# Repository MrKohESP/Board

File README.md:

# Mr. Koh Board
Mr. Koh ESP32-C3 RISC-V Development Board

## The Mr. Koh is a birthday project for Mr. Koh.
# Happy Birthday Mr. Koh! 🥳
Mr. Koh is an Open Hardware, Open Source (GPL3.0), ESP32-C3 RISC-V Developement Board.

## Features
* [RISC-V](https://github.com/jameslzhu/riscv-card/blob/586b60b5c351b3e6e6ebbf7130b9f93013b2e511/riscv-card.pdf) instruction set
* [Espressif Systems ESP32-C3FH4 MCU](https://www.espressif.com/en/products/socs/esp32-c3)
* 400K SDRAM and 4MB Flash memory
* Real-Time Clock support
* 10 GPIOs with RESET, BOOT, and RGB OUT
* [RGB](http://www.world-semi.com/Certifications/details-111-4.html), power and data leds
* Built-in USB Type C flashing and [JTAG debugging](https://docs.espressif.com/projects/esp-idf/en/latest/esp32c3/api-guides/usb-serial-jtag-console.html)
* ESD protected
* [FreeRTOS](https://www.freertos.org/Using-FreeRTOS-on-RISC-V.html) Supported when using [ESP-IDF](https://docs.espressif.com/projects/esp-idf/en/v5.0/esp32/)

## Pinout

## Files
* [Datasheet](https://www.espressif.com/sites/default/files/documentation/esp32-c3_datasheet_en.pdf)
* [Schematic](Schematic.pdf) 
* [BOM](Hardware/Fab/MrKohBOM.csv)
* [CPL (Position)](Hardware/Fab/MrKoh-top-pos.csv)
* [PCB Front](MrKoh.png)
* [PCB Back](MrKohBack.png)

## History
1. v1 Designed 01/23/2023.
2. v1 Sent to production 01/26/2023.
3. v1 Shipped 01/30/2023.
4. v1 Arrival 02/03/2023.
5. v1 Issues with USB Type C connector clearance and USB Type C pinout resulting in connectivity problems.
6. v1 LED was on all the time.
7. Rev 2 Carved out a space for the Type C connector and redid the PCB for correct pinout.
8. Rev 2 Removed Q1 and pull up, Pin GPIO2 is now just an LED.  Reworked PCB to remove Q1 and R7. 
9. Rev 2 Reworked the Pin Header pins to allow 5V from USB and to use that pin in place of USB.
10. Rev 2 Sent to production 02/06/2023, Shenzhen, Guangdong, China Time (UTC+8).
11. Rev 2 pcb finished 02/07/2023
12. Rev 2 assembly finished 2023-02-08 06:37:05 (local time).
13. Rev 2 waiting for Carrier to pick up completed boards.
14. Rev 2 delivered on Mon Feb 13 at 16:43
15. Rev 2 Tests indicate board is fully functional.

## Photo

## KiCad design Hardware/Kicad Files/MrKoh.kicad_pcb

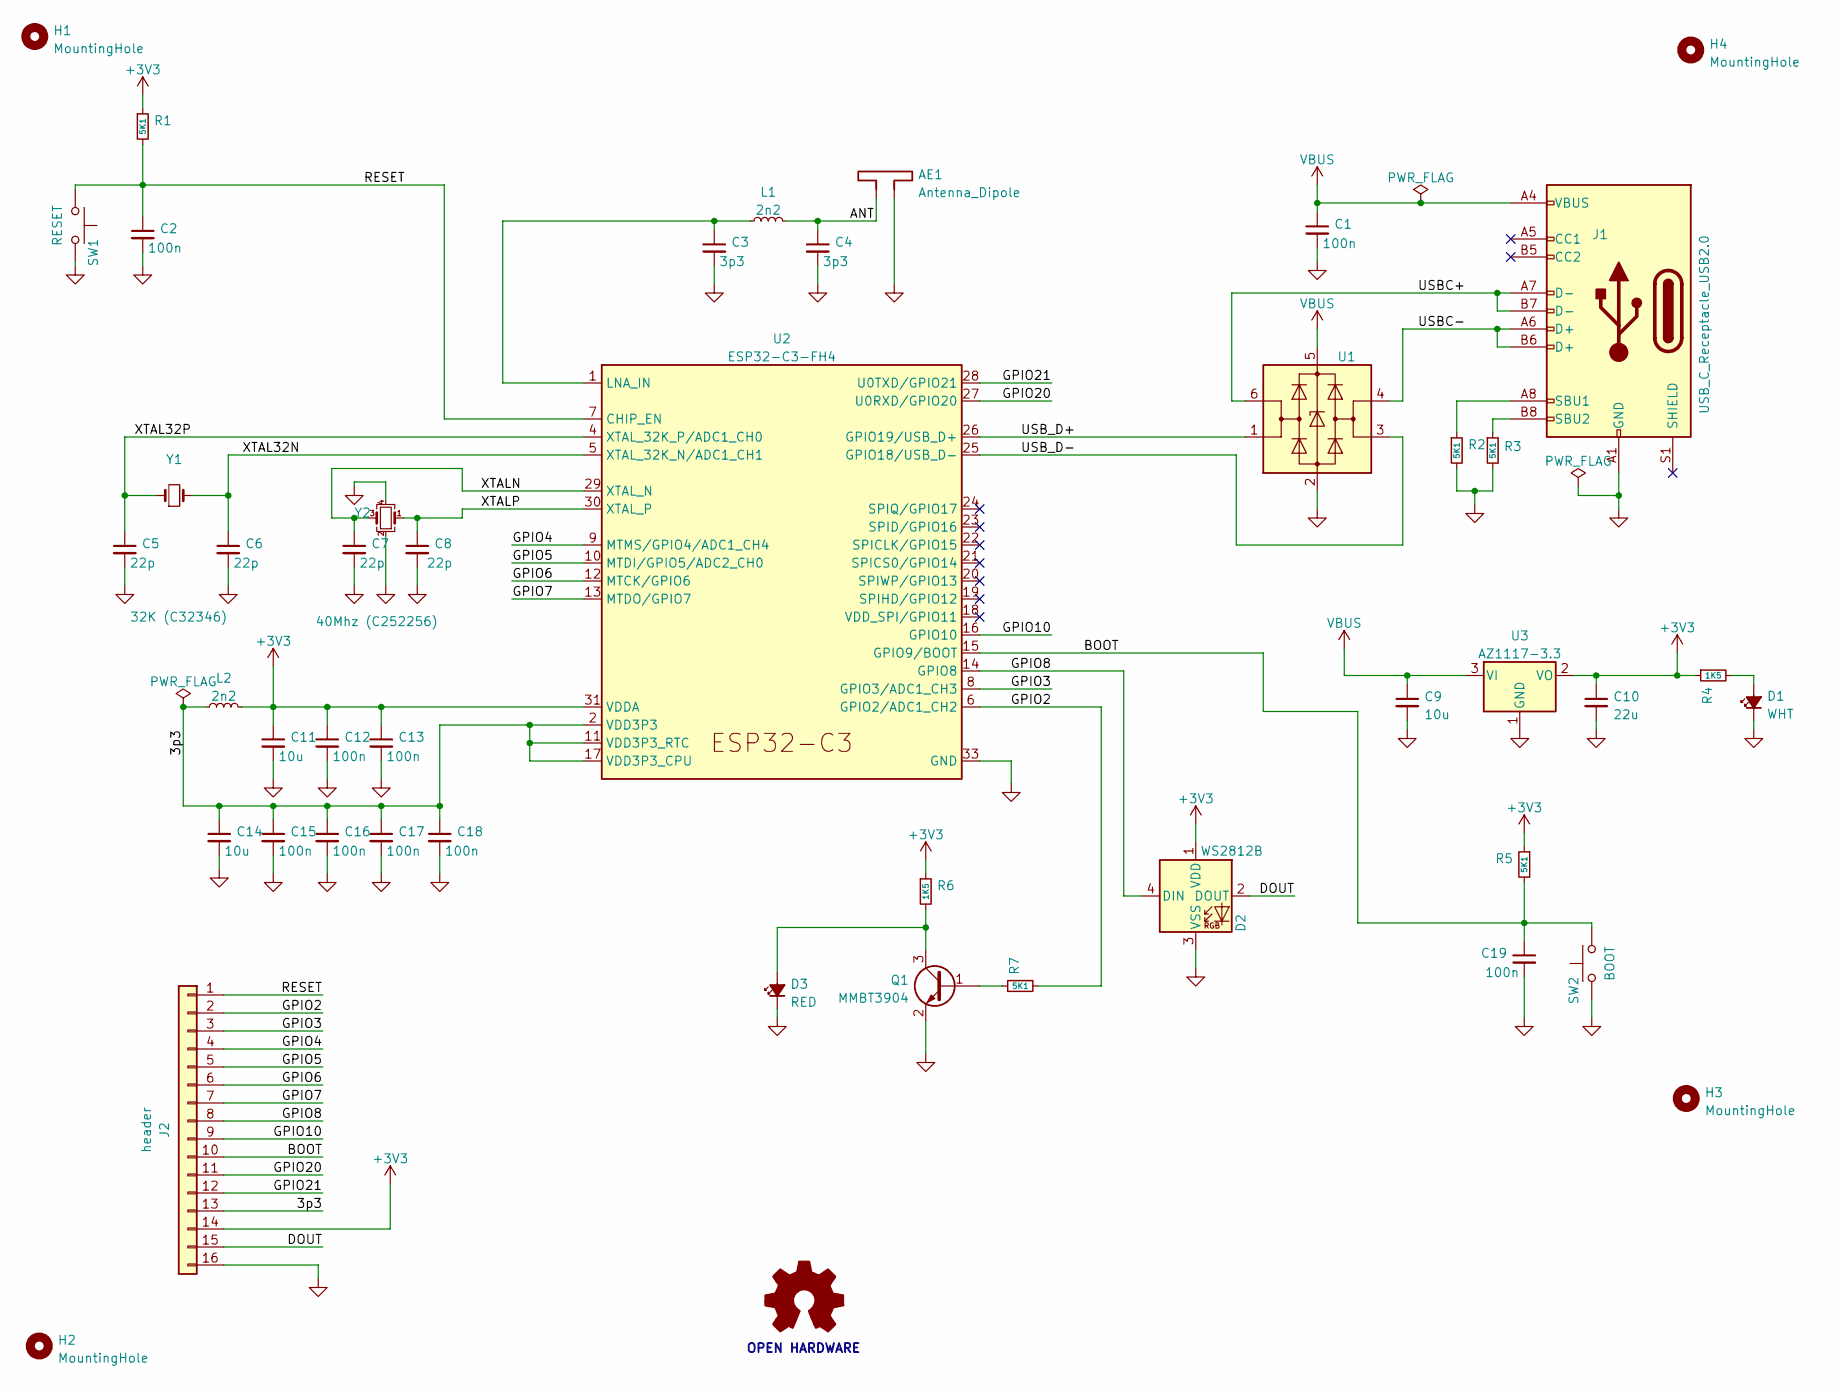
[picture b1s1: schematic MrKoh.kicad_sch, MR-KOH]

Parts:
AE1: Antenna_Dipole; Texas_SWRA117D_2.4GHz_Left
C1, C2, C12, C13, C15, C16, C17, C18, C19: 100n; C_0402_1005Metric; LCSC C60474
C3, C4: 3p3; C_0402_1005Metric; LCSC C1565
C5, C6, C7, C8: 22p; C_0402_1005Metric; LCSC C1555
C9, C11, C14: 10u; C_0603_1608Metric; LCSC C96446
C10: 22u; C_0805_2012Metric; LCSC C45783
D1: WHT; LED_0603_1608Metric; LCSC C2286
D2: WS2812B; LED_WS2812B_PLCC4_5.0x5.0mm_P3.2mm
D3: RED; LED_0603_1608Metric; LCSC C2290
H1, H2, H3, H4: MountingHole; MountingHole_1152_JLCPCB
J1: USB_C_Receptacle_USB2.0; USB_C_Receptacle_HRO_TYPE-C-31-M-12; LCSC C165948
J2: header; PinHeader_1x16_P2.54mm_Vertical
L1, L2: 2n2; L_0402_1005Metric; LCSC C76790
LOGO1: Logo_Open_Hardware_Small; Symbol_GNU-Logo_SilkscreenTop
Q1: MMBT3904; SOT-23; LCSC C20526
R1, R2, R3, R5, R7: 5K1; R_0402_1005Metric; LCSC C25905
R4, R6: 1K5; R_0402_1005Metric; LCSC C25867
SW1: RESET; SW_Push_SPST_NO_Alps_SKRK; LCSC C202388
SW2: BOOT; SW_Push_SPST_NO_Alps_SKRK; LCSC C202388
U1: USBLC6-2SC6; SOT-23-6; LCSC C7519
U2: ESP32-C3-FH4; QFN-32-1EP_5x5mm_P0.5mm_EP3.45x3.45mm; LCSC C2858491
U3: AZ1117-3.3; SOT-223-3_TabPin2; LCSC C92517
Y1: 32K (C32346); Crystal_SMD_3215-2Pin_3.2x1.5mm; LCSC C32346
Y2: 40Mhz (C252256); Crystal_SMD_3225-4Pin_3.2x2.5mm; LCSC C252256

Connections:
+3V3: C10.1, C11.1, C12.1, C13.1, D2.1 (VDD), J2.14, L2.2, R1.1, R4.1, R5.1, R6.1, U2.31 (VDDA), U2.32 (VDDA), U3.2 (VO)
/3p3: C14.1, C15.1, C16.1, C17.1, C18.1, J2.13, L2.1, U2.2 (VDD3P3), U2.3 (VDD3P3), U2.11 (VDD3P3_RTC), U2.17 (VDD3P3_CPU)
/ANT: AE1.1, C4.1, L1.2
/BOOT: C19.1, J2.10, R5.2, SW2.1, U2.15 (GPIO9/BOOT)
/DOUT: D2.2 (DOUT), J2.15
/GPIO2: J2.2, R7.2, U2.6 (GPIO2/ADC1_CH2)
/GPIO3: J2.3, U2.8 (GPIO3/ADC1_CH3)
/GPIO4: J2.4, U2.9 (MTMS/GPIO4/ADC1_CH4)
/GPIO5: J2.5, U2.10 (MTDI/GPIO5/ADC2_CH0)
/GPIO6: J2.6, U2.12 (MTCK/GPIO6)
/GPIO7: J2.7, U2.13 (MTDO/GPIO7)
/GPIO8: D2.4 (DIN), J2.8, U2.14 (GPIO8)
/GPIO10: J2.9, U2.16 (GPIO10)
/GPIO20: J2.11, U2.27 (U0RXD/GPIO20)
/GPIO21: J2.12, U2.28 (U0TXD/GPIO21)
/RESET: C2.1, J2.1, R1.2, SW1.1, U2.7 (CHIP_EN)
/USBC+: J1.A7 (D-), J1.B7 (D-), U1.6 (I/O1)
/USBC-: J1.A6 (D+), J1.B6 (D+), U1.4 (I/O2)
/USB_D+: U1.1 (I/O1), U2.26 (GPIO19/USB_D+)
/USB_D-: U1.3 (I/O2), U2.25 (GPIO18/USB_D-)
/XTAL32N: C6.1, U2.5 (XTAL_32K_N/ADC1_CH1), Y1.2
/XTAL32P: C5.1, U2.4 (XTAL_32K_P/ADC1_CH0), Y1.1
/XTALN: C7.1, U2.29 (XTAL_N), Y2.3
/XTALP: C8.1, U2.30 (XTAL_P), Y2.1
GND: AE1.2, C1.2, C2.2, C3.2, C4.2, C5.2, C6.2, C7.2, C8.2, C9.2, C10.2, C11.2, C12.2, C13.2, C14.2, C15.2, C16.2, C17.2, C18.2, C19.2, D1.1 (K), D2.3 (VSS), D3.1 (K), J1.A1 (GND), J1.A12 (GND), J1.B1 (GND), J1.B12 (GND), J2.16, Q1.2 (E), R2.2, R3.2, SW1.2, SW2.2, U1.2 (GND), U2.33 (GND), U3.1 (GND), Y2.2, Y2.4
unnamed: C3.1, L1.1, U2.1 (LNA_IN)
unnamed: D1.2 (A), R4.2
unnamed: D3.2 (A), Q1.3 (C), R6.2
unnamed: J1.A8 (SBU1), R2.1
unnamed: J1.B8 (SBU2), R3.1
unnamed: Q1.1 (B), R7.1
VBUS: C1.1, C9.1, J1.A4 (VBUS), J1.A9 (VBUS), J1.B4 (VBUS), J1.B9 (VBUS), U1.5 (VBUS), U3.3 (VI)

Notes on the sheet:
OPEN HARDWARE

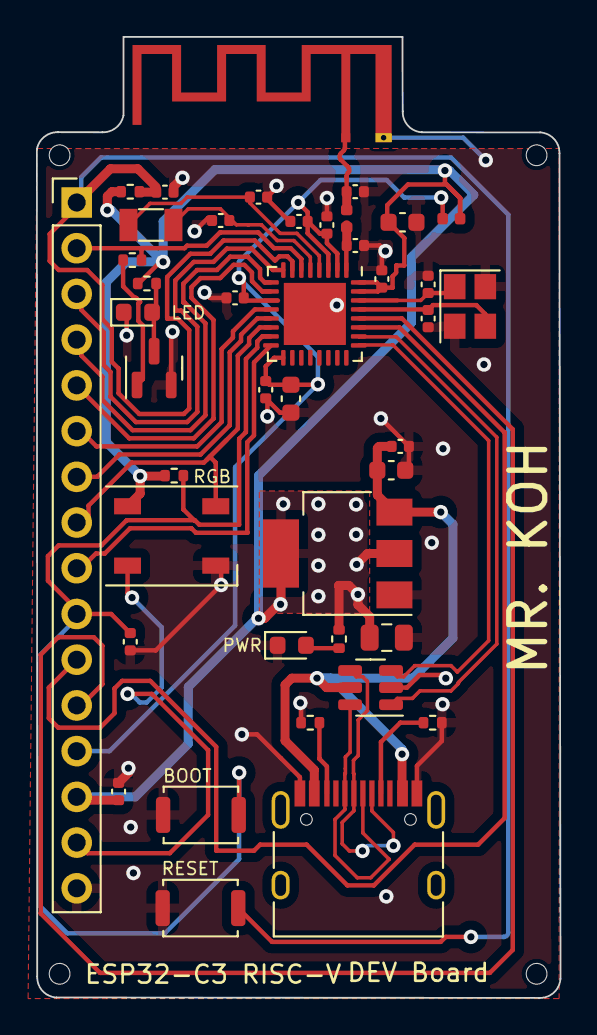
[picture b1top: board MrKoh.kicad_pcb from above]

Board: 2 copper layers, 29.1 x 53.4 mm, 47 parts (1 on the bottom side), 32 nets.

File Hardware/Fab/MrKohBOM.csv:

Comment,Designator,Footprint,LCSC
100n,"C1,C2,C12,C13,C15,C16,C17,C18,C19",Capacitor_SMD:C_0402_1005Metric,C60474
22u,C10,Capacitor_SMD:C_0805_2012Metric,C45783
3p3,"C3,C4",Capacitor_SMD:C_0402_1005Metric,C1565
22p,"C5,C6,C7,C8",Capacitor_SMD:C_0402_1005Metric,C1555
10u,"C9,C11,C14",Capacitor_SMD:C_0603_1608Metric,C96446
USB_C_Receptacle_USB2.0,J1,Connector_USB:USB_C_Receptacle_HRO_TYPE-C-31-M-12,C165948
2n2,"L1,L2",Inductor_SMD:L_0402_1005Metric,C76790
MMBT3904,Q1,Package_TO_SOT_SMD:SOT-23,C20526
5K1,"R1,R2,R3,R5",Resistor_SMD:R_0402_1005Metric,C25905
1K5,"R4,R6",Resistor_SMD:R_0402_1005Metric,C25867
RESET,SW1,Button_Switch_SMD:SW_Push_SPST_NO_Alps_SKRK,C202388
BOOT,SW2,Button_Switch_SMD:SW_Push_SPST_NO_Alps_SKRK,C202388
USBLC6-2SC6,U1,Package_TO_SOT_SMD:SOT-23-6,C7519
ESP32-C3-FH4,U2,Package_DFN_QFN:QFN-32-1EP_5x5mm_P0.5mm_EP3.45x3.45mm,C2858491
AZ1117-3.3,U3,Package_TO_SOT_SMD:SOT-223-3_TabPin2,C92517
32K (C32346),Y1,Crystal:Crystal_SMD_3215-2Pin_3.2x1.5mm,C32346
40Mhz (C252256),Y2,Crystal:Crystal_SMD_3225-4Pin_3.2x2.5mm,C252256
WHT,D1,LED_SMD:LED_0603_1608Metric,C2286
RED,D3,LED_SMD:LED_0603_1608Metric,C2290
WS2812B,D2,LED_SMD:LED_WS2812B_PLCC4_5.0x5.0mm_P3.2mm,C2843785

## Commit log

2023-01-26 Add Board 3D Images
2023-01-26 Added Image
2023-01-26 Schematic
2023-01-26 Fabrication Files
    Fab Files from original order
2023-01-26 Fabrication Files added
    Fab Files From Original Order
2023-01-26 Part issue
    There was a problem with sourcing the original RGB part and changes to schematic, pcb, and fabrication files. Production proofs were added.
2023-01-26 Production time 3d images
2023-01-26 New Part
2023-01-26 Rotate
2023-01-26 Production Zip
    Note changes to the csv files are not updated in the zip file but were uploaded after the fact in the bom and pos order proccess.
2023-01-27 Rename Hardware/Fabrication Files/espc4synth-B_Cu.gbl to Hardware/Fab/MrKoh.gbl
2023-01-27 Rename Hardware/Fabrication Files/espc4synth-B_Mask.gbs to Hardware/Fab/MrKoh-B_Mask.gbs
2023-01-27 Rename Hardware/Fabrication Files/espc4synth-B_Paste.gbp to Hardware/Fab/MrKoh-B_Paste.gbp
2023-01-27 Rename Hardware/Fabrication Files/espc4synth-B_Silkscreen.gbo to Hardware/Fab/MrKoh-B_Silkscreen.gbo
2023-01-27 Rename Hardware/Fabrication Files/espc4synth-Edge_Cuts.gm1 to Hardware/Fab/MrKoh-Edge_Cuts.gm1
2023-01-27 Rename Hardware/Fabrication Files/espc4synth-F_Cu.gtl to Hardware/Fab/MrKoh-F_Cu.gtl
2023-01-27 Rename Hardware/Fabrication Files/espc4synth-F_Mask.gts to Hardware/Fab/MrKoh-F_Mask.gts
2023-01-27 Rename Hardware/Fabrication Files/espc4synth-F_Paste.gtp to Hardware/Fab/MrKoh-F_Paste.gtp
2023-01-27 Rename Hardware/Fabrication Files/espc4synth-F_Silkscreen.gto to Hardware/Fab/MrKoh-F_Silkscreen.gto
2023-01-27 Rename Hardware/Fabrication Files/espc4synth-drl_map.gbr to Hardware/Fab/MrKoh-drl_map.gbr
2023-01-27 Rename Hardware/Fabrication Files/espc4synth-job.gbrjob to Hardware/Fab/MrKoh-job.gbrjob
2023-01-27 Rename Hardware/Fabrication Files/espc4synth-top-pos.csv to Hardware/Fab/MrKoh-position.csv
2023-01-27 Rename Hardware/Fabrication Files/espc4synth.csv to Hardware/Fab/MrKoh_BOM.csv
2023-01-27 Rename Hardware/Fabrication Files/espc4synth.drl to Hardware/Fab/MrKoh.drl
2023-01-27 Rename Hardware/Kicad Files/MrKoh.kicad_pcb to Hardware/KiCad/MrKoh.kicad_pcb
2023-01-27 Rename Hardware/Kicad Files/MrKoh.kicad_pro to Hardware/KiCad/MrKoh.kicad_pro
2023-01-27 Rename Hardware/Kicad Files/MrKoh.kicad_sch to Hardware/KiCad/MrKoh.kicad_sch
2023-01-27 Production Zip
2023-02-06 v2 Fab Files
2023-02-06 v2 file refresh
2023-02-06 Birthday Emoji
2023-02-06 Move v2 changes
2023-02-06 REV 2
2023-02-08 Pinout Viso Drawing
2023-02-09 Rev 2 Shipped
2023-02-22 photo physical board
2023-02-22 Update with actual photo
